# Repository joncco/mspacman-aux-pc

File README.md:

This is a reproduction of the MS PAC-MAN AUX PC board used in Midway's Pac-Man arcade PCB.

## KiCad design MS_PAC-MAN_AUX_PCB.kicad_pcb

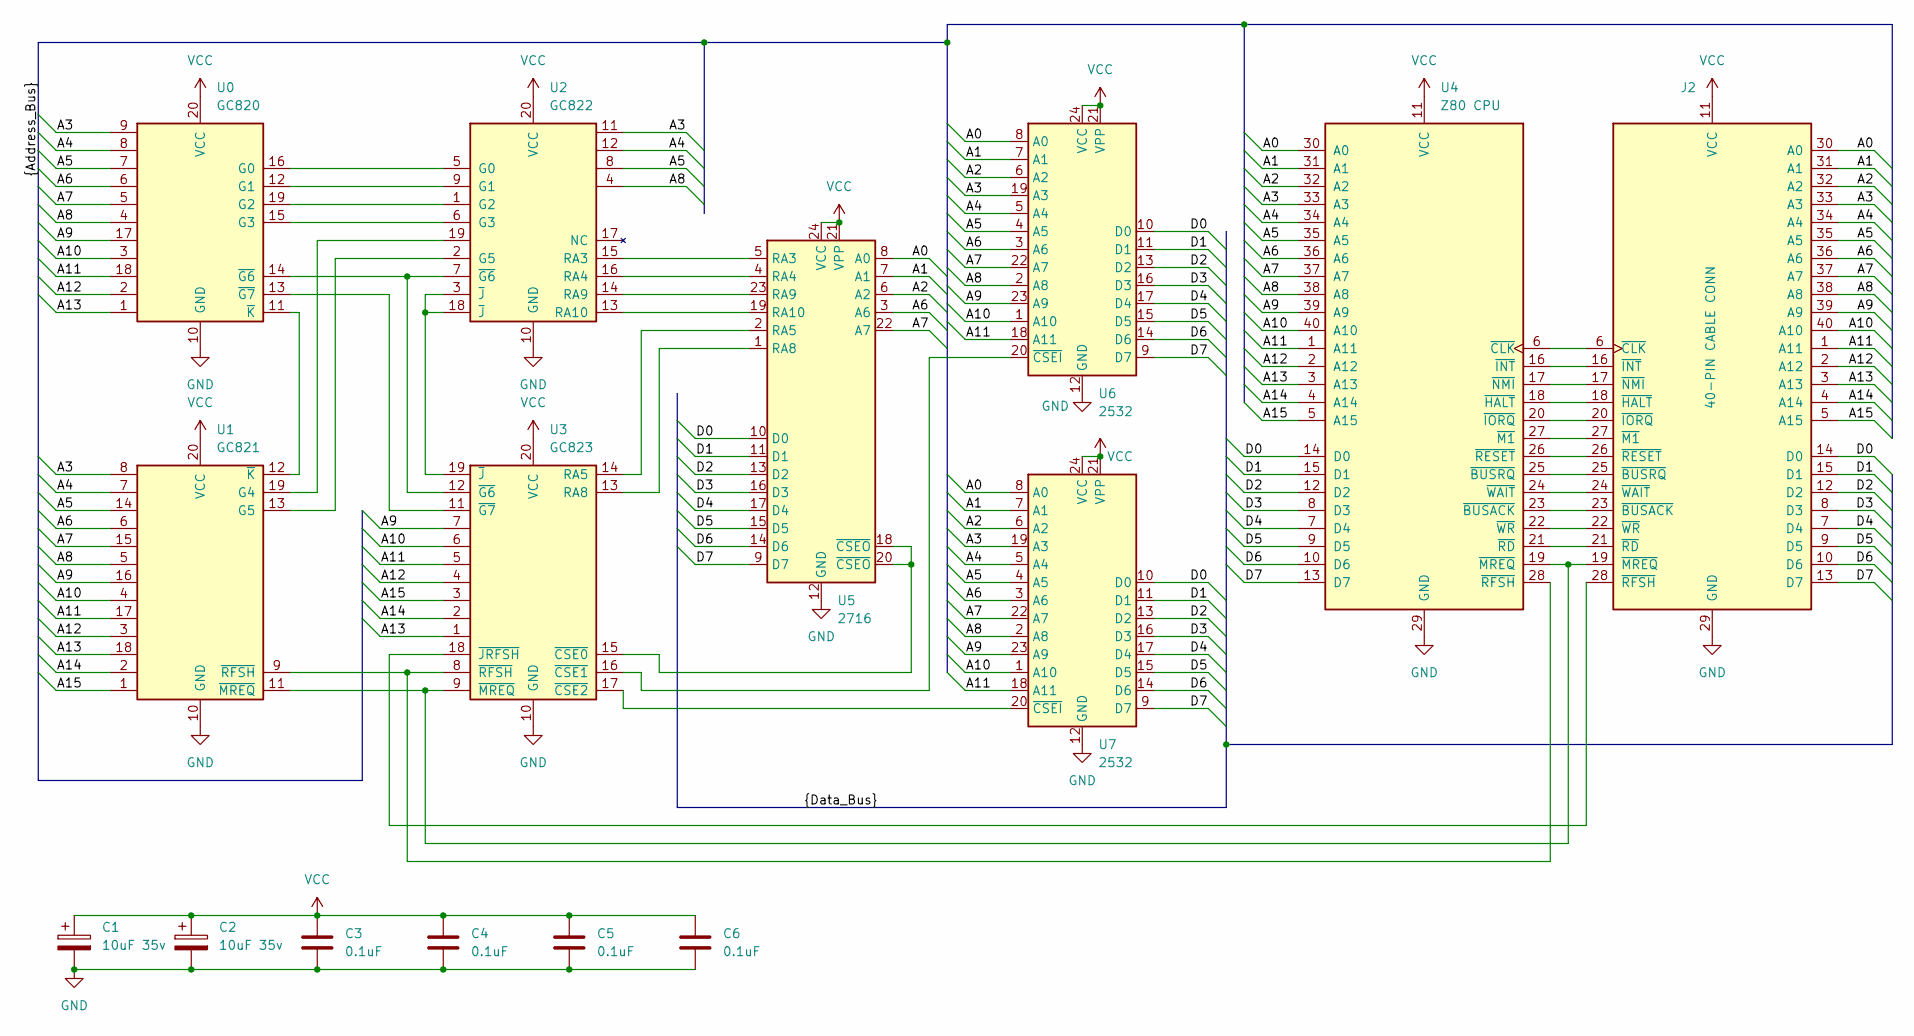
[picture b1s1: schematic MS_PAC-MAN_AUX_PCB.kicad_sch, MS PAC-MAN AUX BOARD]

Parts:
C1, C2: 10uF 35v; CP_Axial_L11.0mm_D6.0mm_P18.00mm_Horizontal
C3, C4, C5, C6: 0.1uF; C_Axial_L3.8mm_D2.5mm_P12.685mm_Horizontal
J2: 40-PIN CABLE CONN; DIP-40_W15.24mm_LongPads
U0: GC820; DIP-20_W7.62mm_LongPads
U1: GC821; DIP-20_W7.62mm_LongPads
U2: GC822; DIP-20_W7.62mm_LongPads
U3: GC823; DIP-20_W7.62mm_LongPads
U4: Z80 CPU; DIP-40_W15.24mm_LongPads
U5: 2716; DIP-24_W15.24mm_LongPads
U6, U7: 2532; DIP-24_W15.24mm_LongPads

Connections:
/A0: U4.30 (A0), U5.8 (A0), U6.8 (A0), U7.8 (A0); also elsewhere on the board
/A1: U4.31 (A1), U5.7 (A1), U6.7 (A1), U7.7 (A1); also elsewhere on the board
/A2: U4.32 (A2), U5.6 (A2), U6.6 (A2), U7.6 (A2); also elsewhere on the board
/A3: U0.9, U1.8, U2.11, U4.33 (A3), U6.19 (A3), U7.19 (A3); also elsewhere on the board
/A4: U0.8, U1.7, U2.12, U4.34 (A4), U6.5 (A4), U7.5 (A4); also elsewhere on the board
/A5: U0.7, U1.14, U2.8, U4.35 (A5), U6.4 (A5), U7.4 (A5); also elsewhere on the board
/A6: U0.6, U1.6, U4.36 (A6), U5.3 (A6), U6.3 (A6), U7.3 (A6); also elsewhere on the board
/A7: U0.5, U1.15, U4.37 (A7), U5.22 (A7), U6.22 (A7), U7.22 (A7); also elsewhere on the board
/A8: U0.4, U1.5, U2.4, U4.38 (A8), U6.2 (A8), U7.2 (A8); also elsewhere on the board
/A9: U0.17, U1.16, U3.7, U4.39 (A9), U6.23 (A9), U7.23 (A9); also elsewhere on the board
/A10: U0.3, U1.4, U3.6, U4.40 (A10), U6.1 (A10), U7.1 (A10); also elsewhere on the board
/A11: U0.18, U1.17, U3.5, U4.1 (A11), U6.18 (A11), U7.18 (A11); also elsewhere on the board
/A12: U0.2, U1.3, U3.4, U4.2 (A12); also elsewhere on the board
/A13: U0.1, U1.18, U3.1, U4.3 (A13); also elsewhere on the board
/A14: U1.2, U3.2, U4.4 (A14); also elsewhere on the board
/A15: U1.1, U3.3, U4.5 (A15); also elsewhere on the board
/D0: U4.14 (D0), U5.10 (D0), U6.10 (D0), U7.10 (D0); also elsewhere on the board
/D1: U4.15 (D1), U5.11 (D1), U6.11 (D1), U7.11 (D1); also elsewhere on the board
/D2: U4.12 (D2), U5.13 (D2), U6.13 (D2), U7.13 (D2); also elsewhere on the board
/D3: U4.8 (D3), U5.16 (D3), U6.16 (D3), U7.16 (D3); also elsewhere on the board
/D4: U4.7 (D4), U5.17 (D4), U6.17 (D4), U7.17 (D4); also elsewhere on the board
/D5: U4.9 (D5), U5.15 (D5), U6.15 (D5), U7.15 (D5); also elsewhere on the board
/D6: U4.10 (D6), U5.14 (D6), U6.14 (D6), U7.14 (D6); also elsewhere on the board
/D7: U4.13 (D7), U5.9 (D7), U6.9 (D7), U7.9 (D7); also elsewhere on the board
GND: C1.2, C2.2, C3.2, C4.2, C5.2, C6.2, U0.10 (GND), U1.10 (GND), U2.10 (GND), U3.10 (GND), U4.29 (GND), U5.12 (GND), U6.12 (GND), U7.12 (GND); also elsewhere on the board
unnamed 25: U4.23 (~BUSACK); also elsewhere on the board
unnamed 26: U4.25 (~BUSRQ); also elsewhere on the board
unnamed 27: U4.6 (~CLK); also elsewhere on the board
unnamed 28: U4.18 (~HALT); also elsewhere on the board
unnamed 29: U4.16 (~INT); also elsewhere on the board
unnamed 30: U4.20 (~IORQ); also elsewhere on the board
unnamed 31: U4.27 (~M1); also elsewhere on the board
unnamed 32: U1.11 (~MREQ), U3.9 (~MREQ), U4.19 (~MREQ); also elsewhere on the board
unnamed 33: U4.17 (~NMI); also elsewhere on the board
unnamed 34: U4.21 (~RD); also elsewhere on the board
unnamed 35: U4.26 (~RESET); also elsewhere on the board
unnamed 36: U3.18 (~JRFSH); also elsewhere on the board
unnamed 37: U4.24 (~WAIT); also elsewhere on the board
unnamed 38: U4.22 (~WR); also elsewhere on the board
unnamed: U0.16 (G0), U2.5 (G0)
unnamed: U0.12 (G1), U2.9 (G1)
unnamed: U0.19 (G2), U2.1 (G2)
unnamed: U0.15 (G3), U2.6 (G3)
unnamed: U0.14 (~G6), U2.7 (~G6), U3.12 (~G6)
unnamed: U0.13 (~G7), U3.11 (~G7)
unnamed: U0.11 (~K), U1.12 (~K)
unnamed: U1.19 (G4), U2.19
unnamed: U1.13 (G5), U2.2 (G5)
unnamed: U1.9 (~RFSH), U3.8 (~RFSH), U4.28 (~RFSH)
unnamed: U2.15 (RA3), U5.5 (RA3)
unnamed: U2.16 (RA4), U5.4 (RA4)
unnamed: U2.14 (RA9), U5.23 (RA9)
unnamed: U2.13 (RA10), U5.19 (RA10)
unnamed: U3.14 (RA5), U5.2 (RA5)
unnamed: U3.13 (RA8), U5.1 (RA8)
unnamed: U3.15 (~CSE0), U5.18 (~CSEO), U5.20 (~CSEO)
unnamed: U3.16 (~CSE1), U6.20 (~CSEI)
unnamed: U3.17 (~CSE2), U7.20 (~CSEI)
unnamed: U2.3 (~J), U2.18 (~J), U3.19 (~J)
VCC: C1.1, C2.1, C3.1, C4.1, C5.1, C6.1, U0.20 (VCC), U1.20 (VCC), U2.20 (VCC), U3.20 (VCC), U4.11 (VCC), U5.21 (VPP), U5.24 (VCC), U6.21 (VPP), U6.24 (VCC), U7.21 (VPP), U7.24 (VCC); also elsewhere on the board

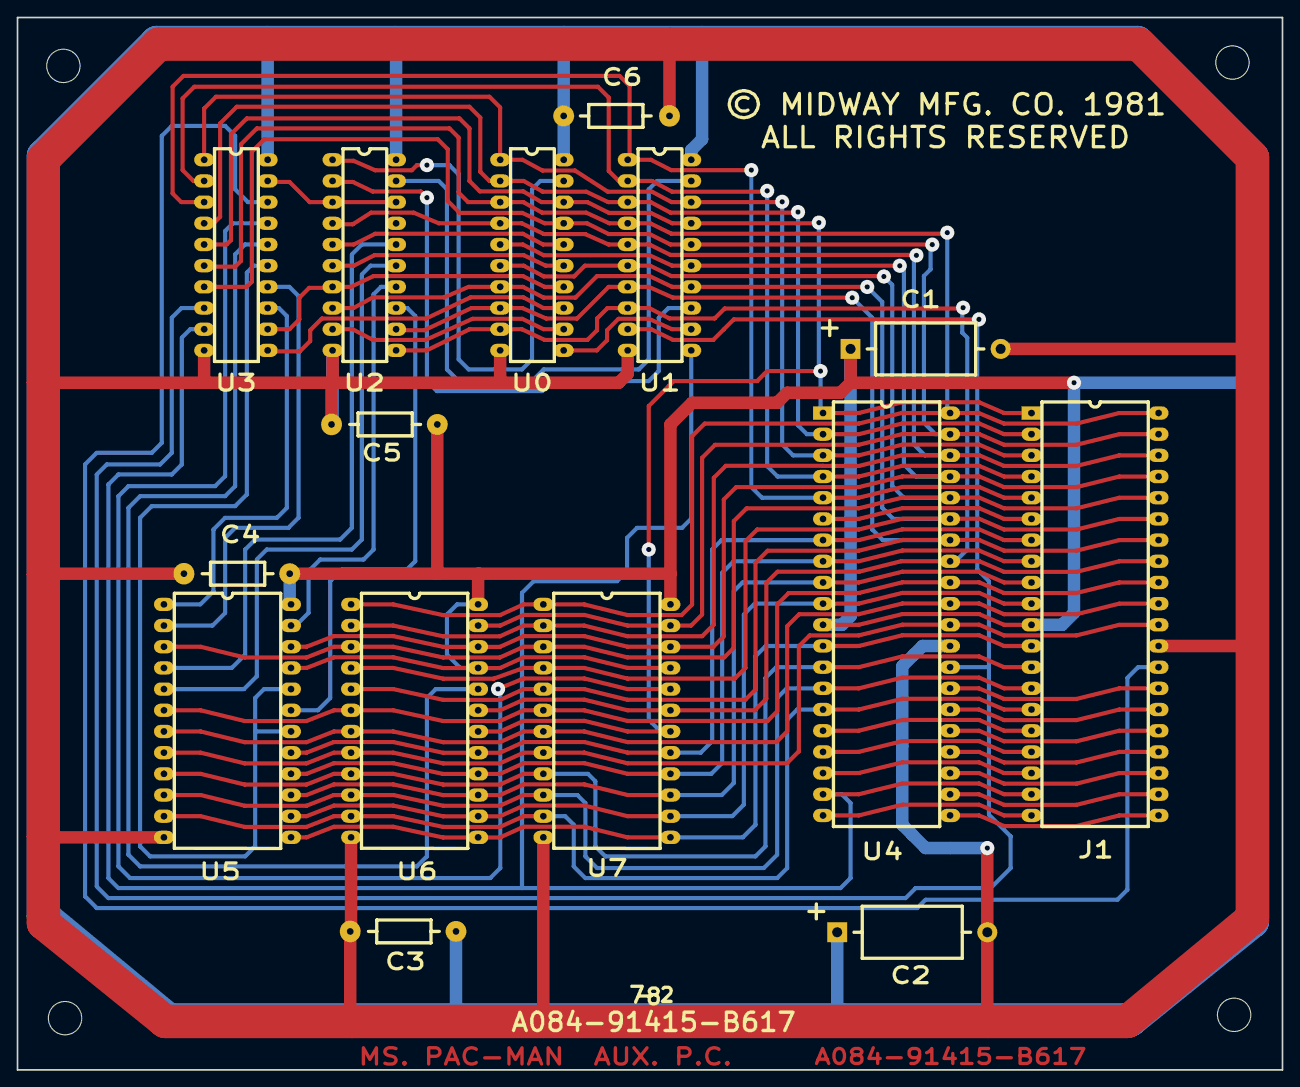
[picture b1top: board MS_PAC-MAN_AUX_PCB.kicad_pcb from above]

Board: 2 copper layers, 151.7 x 126.2 mm, 15 parts (0 on the bottom side), 60 nets.

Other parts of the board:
J1: 40-PIN CABLE CONN; DIP-40_W15.24mm_LongPads

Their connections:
/A0: J1.30 (A0); also elsewhere on the board
/A1: J1.31 (A1); also elsewhere on the board
/A2: J1.32 (A2); also elsewhere on the board
/A3: J1.33 (A3); also elsewhere on the board
/A4: J1.34 (A4); also elsewhere on the board
/A5: J1.35 (A5); also elsewhere on the board
/A6: J1.36 (A6); also elsewhere on the board
/A7: J1.37 (A7); also elsewhere on the board
/A8: J1.38 (A8); also elsewhere on the board
/A9: J1.39 (A9); also elsewhere on the board
/A10: J1.40 (A10); also elsewhere on the board
/A11: J1.1 (A11); also elsewhere on the board
/A12: J1.2 (A12); also elsewhere on the board
/A13: J1.3 (A13); also elsewhere on the board
/A14: J1.4 (A14); also elsewhere on the board
/A15: J1.5 (A15); also elsewhere on the board
/D0: J1.14 (D0); also elsewhere on the board
/D1: J1.15 (D1); also elsewhere on the board
/D2: J1.12 (D2); also elsewhere on the board
/D3: J1.8 (D3); also elsewhere on the board
/D4: J1.7 (D4); also elsewhere on the board
/D5: J1.9 (D5); also elsewhere on the board
/D6: J1.10 (D6); also elsewhere on the board
/D7: J1.13 (D7); also elsewhere on the board
GND: J1.29 (GND); also elsewhere on the board
unnamed 25: J1.23 (~BUSACK); also elsewhere on the board
unnamed 26: J1.25 (~BUSRQ); also elsewhere on the board
unnamed 27: J1.6 (~CLK); also elsewhere on the board
unnamed 28: J1.18 (~HALT); also elsewhere on the board
unnamed 29: J1.16 (~INT); also elsewhere on the board
unnamed 30: J1.20 (~IORQ); also elsewhere on the board
unnamed 31: J1.27 (~M1); also elsewhere on the board
unnamed 32: J1.19 (~MREQ); also elsewhere on the board
unnamed 33: J1.17 (~NMI); also elsewhere on the board
unnamed 34: J1.21 (~RD); also elsewhere on the board
unnamed 35: J1.26 (~RESET); also elsewhere on the board
unnamed 36: J1.28 (~RFSH); also elsewhere on the board
unnamed 37: J1.24 (~WAIT); also elsewhere on the board
unnamed 38: J1.22 (~WR); also elsewhere on the board
VCC: J1.11 (VCC); also elsewhere on the board

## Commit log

2024-12-12 Add CC-BY-4.0 License

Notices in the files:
MS_PAC-MAN_AUX_PCB.kicad_pcb:
© MIDWAY MFG. CO. 1981
ALL RIGHTS RESERVED
